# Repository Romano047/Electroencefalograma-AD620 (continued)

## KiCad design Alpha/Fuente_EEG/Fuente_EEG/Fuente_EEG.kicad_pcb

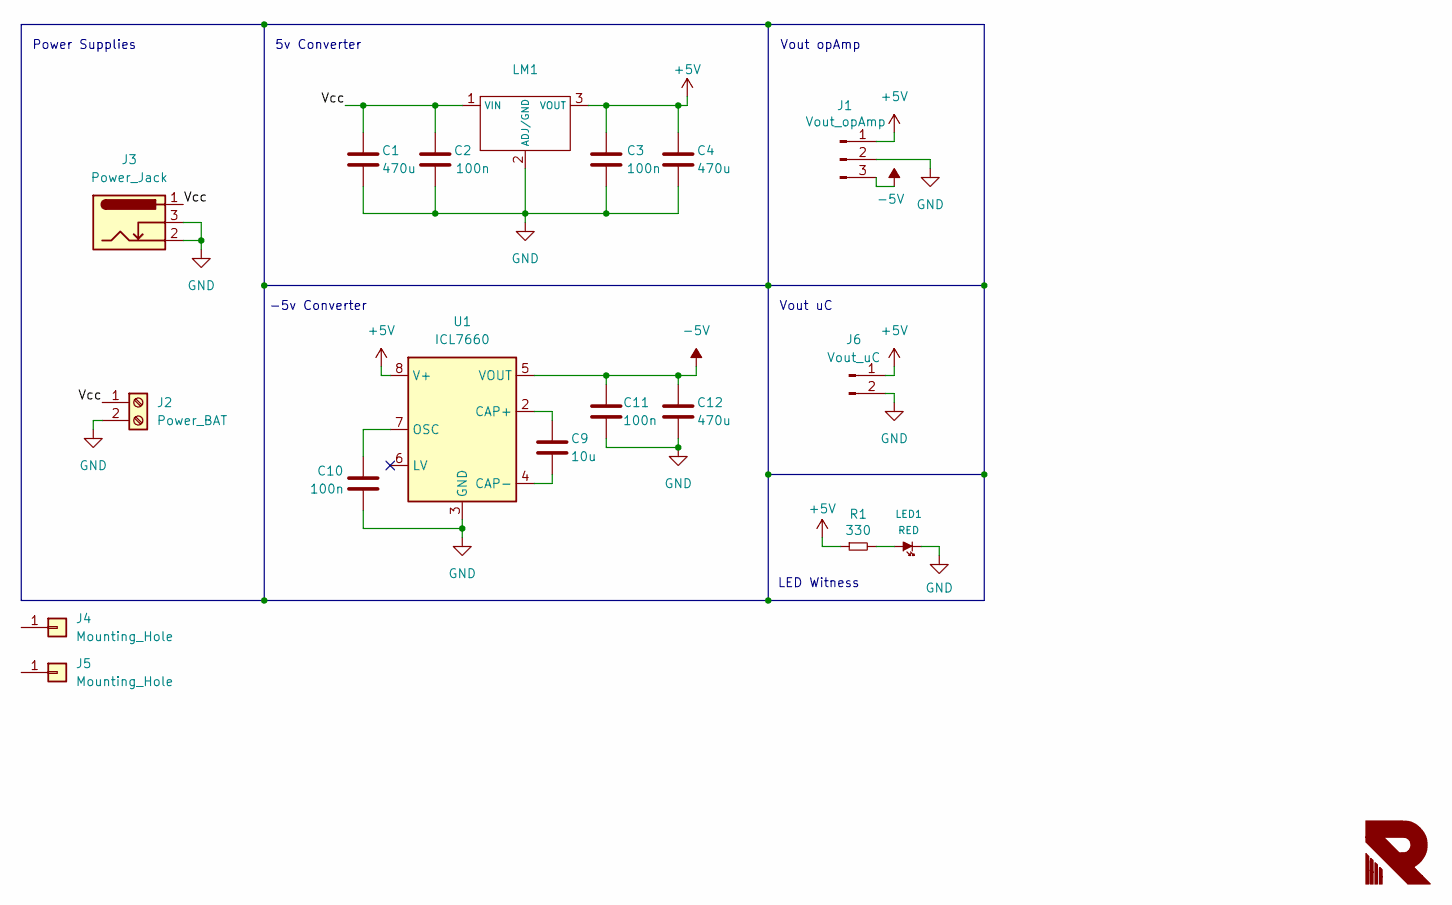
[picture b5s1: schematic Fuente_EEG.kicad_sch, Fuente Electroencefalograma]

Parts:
C1, C4, C12: 470u; CAP_ELEC_5x11mm
C2, C3, C10, C11: 100n; C_0805
C9: 10u; CAP_ELEC_5x11mm
J1: Vout_opAmp; Molex_KK-254_AE-6410-03A_1x03_P2.54mm_Vertical
J2: Power_BAT; BORNERA2_DUO
J3: Power_Jack; BarrelJack_Horizontal
J4, J5: Mounting_Hole; hole_2mm
J6: Vout_uC; Molex_KK-254_AE-6410-02A_1x02_P2.54mm_Vertical
LED1: RED; led_3mm_red
LM1: SOT223-TAB2
R1: 330; R_0805
U1: ICL7660; SOIC-8_3.9x4.9mm_P1.27mm

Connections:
+5V: C3.1, C4.1, J1.1, J6.1, LM1.3 (VOUT), R1.1, U1.8 (V+)
-5V: C11.1, C12.1, J1.3, U1.5 (VOUT)
/Vcc: C1.1, C2.1, J2.1, J3.1, LM1.1 (VIN)
GND: C1.2, C2.2, C3.2, C4.2, C10.2, C11.2, C12.2, J1.2, J2.2, J3.2, J3.3, J6.2, LED1.2 (K), LM1.2 (ADJ/GND), U1.3 (GND)
unnamed: LED1.1 (A), R1.2
unnamed: C9.1, U1.2 (CAP+)
unnamed: C9.2, U1.4 (CAP-)
unnamed: C10.1, U1.7 (OSC)

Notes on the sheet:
Power Supplies
-5v Converter
Vout opAmp
Vout uC
LED Witness
5v Converter

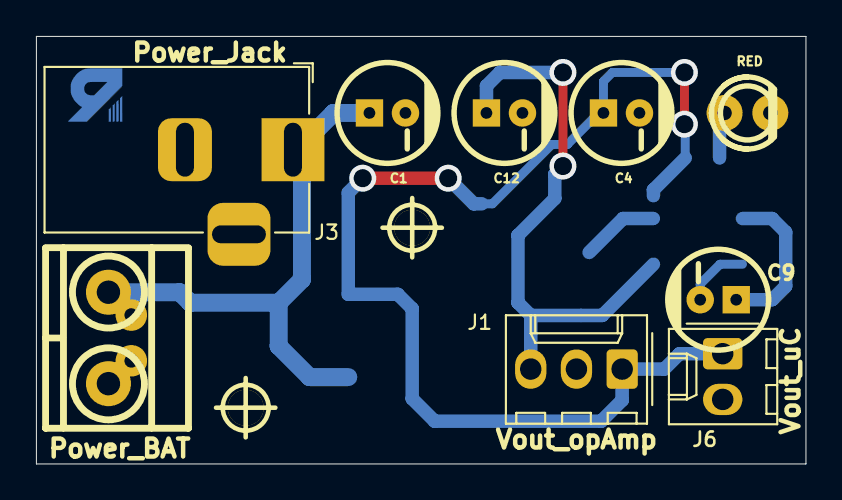
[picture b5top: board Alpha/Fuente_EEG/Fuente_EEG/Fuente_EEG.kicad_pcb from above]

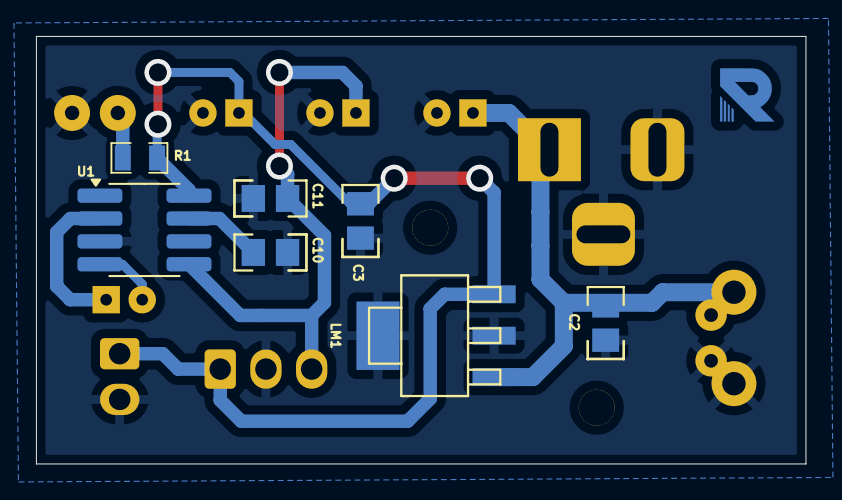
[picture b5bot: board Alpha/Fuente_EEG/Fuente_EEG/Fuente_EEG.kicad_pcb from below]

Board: 2 copper layers, 42.8 x 23.8 mm, 18 parts (7 on the bottom side), 8 nets.

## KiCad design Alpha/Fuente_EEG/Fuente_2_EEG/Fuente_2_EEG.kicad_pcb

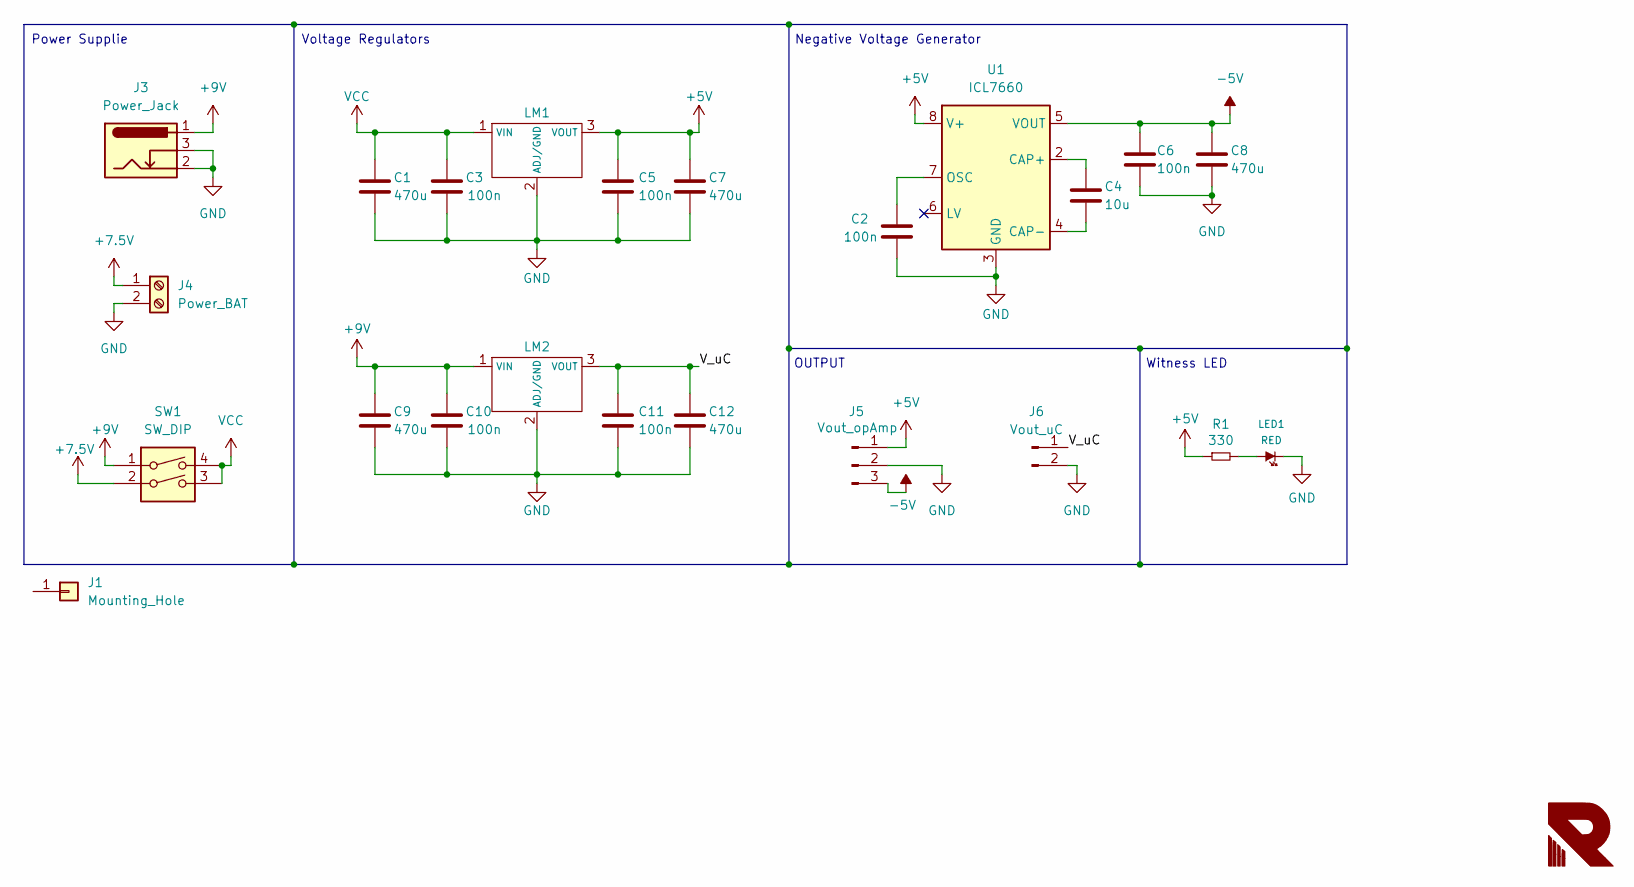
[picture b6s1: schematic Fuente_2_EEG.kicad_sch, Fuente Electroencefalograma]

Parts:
C1, C7, C8, C9, C12: 470u; CAP_ELEC_8x11.5mm
C2, C3, C5, C6, C10, C11: 100n; C_0805
C4: 10u; CAP_ELEC_5x11mm
J1: Mounting_Hole; hole_2mm
J3: Power_Jack; BarrelJack_Horizontal
J4: Power_BAT; BORNERA2_DUO
J5: Vout_opAmp; Molex_KK-254_AE-6410-03A_1x03_P2.54mm_Vertical
J6: Vout_uC; Molex_KK-254_AE-6410-02A_1x02_P2.54mm_Vertical
LED1: RED; led_3mm_red
LM1, LM2: TO-220-2
R1: 330; R_0805
SW1: SW_DIP; SW_DIP_SPSTx02_Slide_9.78x7.26mm_W7.62mm_P2.54mm
U1: ICL7660; DIP-8

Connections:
+5V: C5.1, C7.1, J5.1, LM1.3 (VOUT), R1.1, U1.8 (V+)
+7.5V: J4.1, SW1.2
+9V: C9.1, C10.1, J3.1, LM2.1 (VIN), SW1.1
-5V: C6.1, C8.1, J5.3, U1.5 (VOUT)
/V_uC: C11.1, C12.1, J6.1, LM2.3 (VOUT)
GND: C1.2, C2.2, C3.2, C5.2, C6.2, C7.2, C8.2, C9.2, C10.2, C11.2, C12.2, J3.2, J3.3, J4.2, J5.2, J6.2, LED1.2 (K), LM1.2 (ADJ/GND), LM2.2 (ADJ/GND), U1.3 (GND)
unnamed: LED1.1 (A), R1.2
unnamed: C4.1, U1.2 (CAP+)
unnamed: C4.2, U1.4 (CAP-)
unnamed: C2.1, U1.7 (OSC)
VCC: C1.1, C3.1, LM1.1 (VIN), SW1.3, SW1.4

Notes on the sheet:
Power Supplie
Witness LED
Voltage Regulators
OUTPUT
Negative Voltage Generator

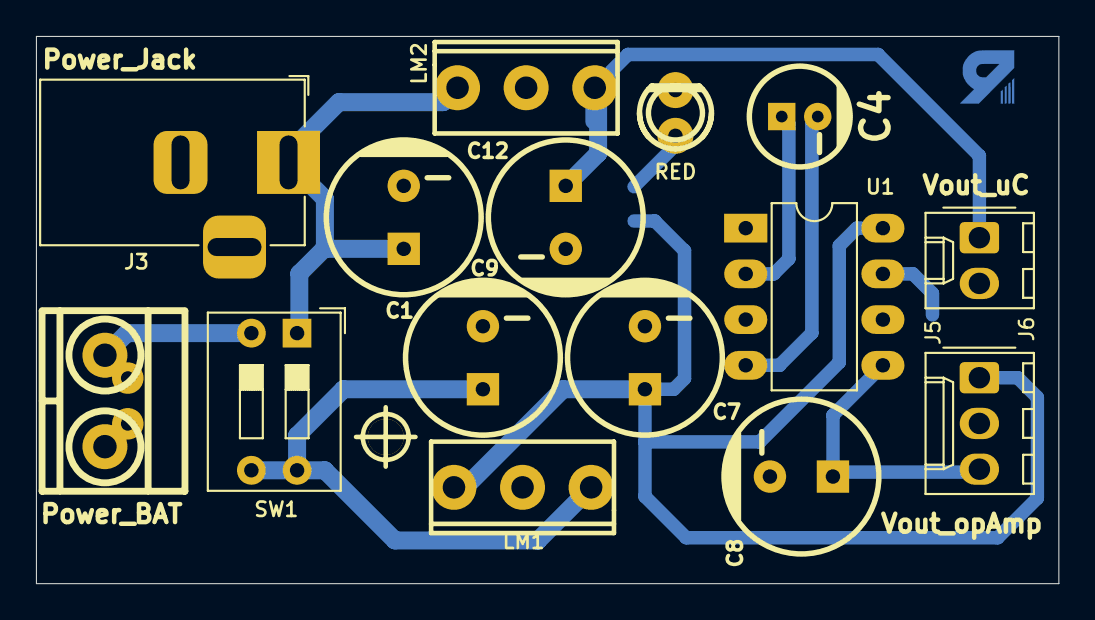
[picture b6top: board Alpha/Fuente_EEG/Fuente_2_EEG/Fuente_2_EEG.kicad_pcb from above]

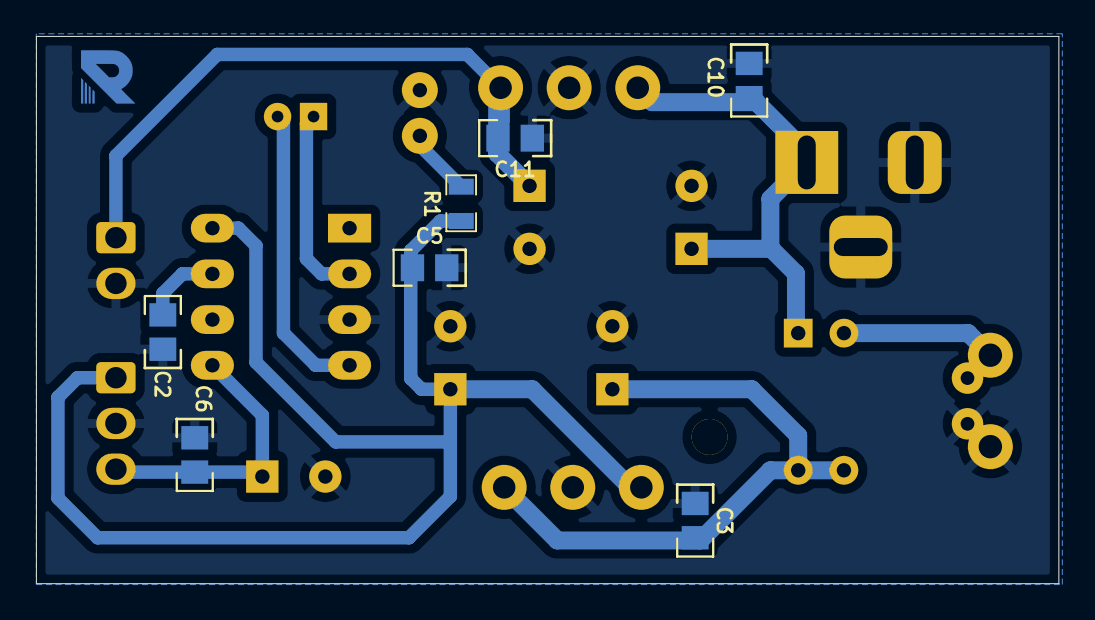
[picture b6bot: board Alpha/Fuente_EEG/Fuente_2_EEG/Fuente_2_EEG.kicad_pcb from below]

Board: 2 copper layers, 56.8 x 30.4 mm, 23 parts (7 on the bottom side), 11 nets.

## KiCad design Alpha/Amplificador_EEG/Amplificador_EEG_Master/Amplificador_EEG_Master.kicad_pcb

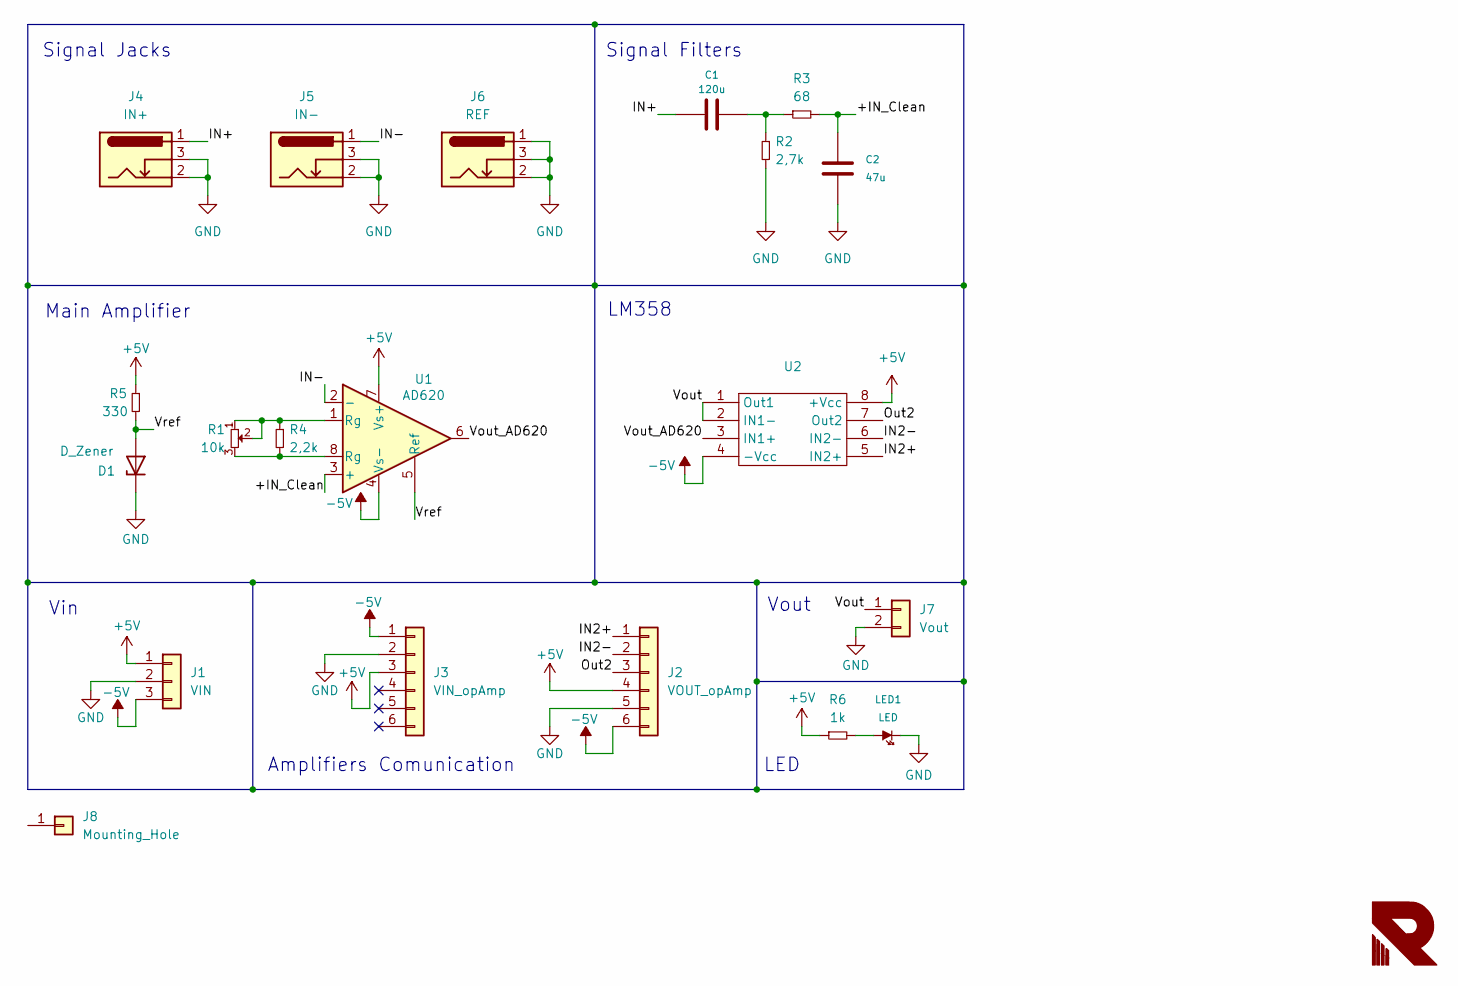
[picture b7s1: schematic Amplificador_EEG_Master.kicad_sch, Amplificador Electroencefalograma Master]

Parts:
C1: 120u; CAP_ELEC_5x11mm
C2: 47u; CAP_ELEC_5x11mm
D1: D_Zener; RES0.2
J1: VIN; Molex_KK-254_AE-6410-03A_1x03_P2.54mm_Vertical
J2: VOUT_opAmp; Molex_KK-254_AE-6410-06A_1x06_P2.54mm_Vertical
J3: VIN_opAmp; Molex_KK-254_AE-6410-06A_1x06_P2.54mm_Vertical
J4: IN+; BarrelJack_Horizontal
J5: IN-; BarrelJack_Horizontal
J6: REF; BarrelJack_Horizontal
J7: Vout; Molex_KK-254_AE-6410-02A_1x02_P2.54mm_Vertical
J8: Mounting_Hole; hole_2mm
LED1: LED; LED_1206
R1: 10k; Potenciometer_Trimpot
R2: 2,7k; RES0.3
R3: 68; RES0.3
R4: 2,2k; RES0.3
R5: 330; R_0805
R6: 1k; R_0805
U1: AD620; DIP-8_W7.62mm_LongPads
U2: SSOP-8

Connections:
+5V: J1.1, J2.4, J3.3, R5.1, R6.1, U1.7 (Vs+), U2.8 (+Vcc)
-5V: J1.3, J2.6, J3.1, U1.4 (Vs-), U2.4 (-Vcc)
/+IN_Clean: C2.2, R3.2, U1.3 (+)
/IN2+: J2.1, U2.5 (IN2+)
/IN2-: J2.2, U2.6 (IN2-)
/IN+: C1.1, J4.1
/IN-: J5.1, U1.2 (-)
/Out2: J2.3, U2.7 (Out2)
/Vout: J7.1, U2.1 (Out1), U2.2 (IN1-)
/Vout_AD620: U1.6, U2.3 (IN1+)
/Vref: D1.2 (A), R5.2, U1.5 (Ref)
GND: C2.1, D1.1 (K), J1.2, J2.5, J3.2, J4.2, J4.3, J5.2, J5.3, J6.1, J6.2, J6.3, J7.2, LED1.2 (K), R2.2
unnamed: C1.2, R2.1, R3.1
unnamed: LED1.1 (A), R6.2
unnamed: R1.1, R1.2, R4.1, U1.1 (Rg)
unnamed: R1.3, R4.2, U1.8 (Rg)

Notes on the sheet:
Vin
Signal Filters
LED
Vout
LM358
Signal Jacks
Main Amplifier
Amplifiers Comunication

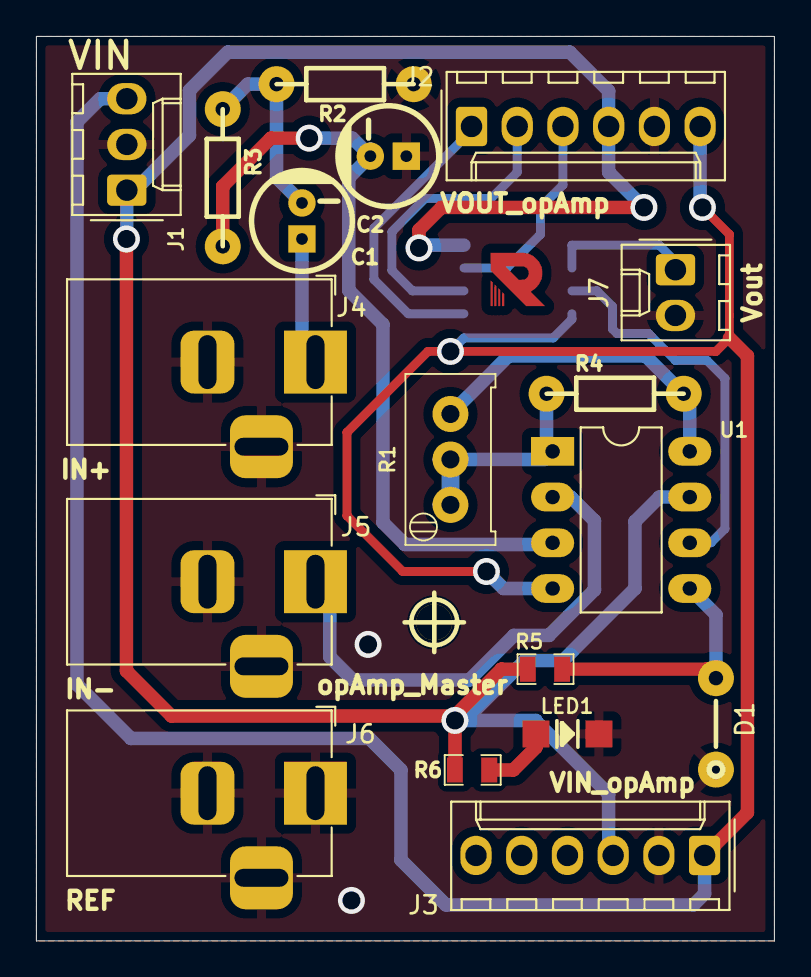
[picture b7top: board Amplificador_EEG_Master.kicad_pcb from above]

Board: 2 copper layers, 41.0 x 50.2 mm, 20 parts (1 on the bottom side), 16 nets.

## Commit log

2025-05-16 Create Software
2025-06-21 Carpeta Beta
2025-06-21 Limpieza de rama Alpha
2025-06-21 Archivos de versión Alpha
2025-06-21 Archivos versión Beta
2025-06-21 Limpieza de Rama Beta
2025-06-21 Última Actualización de Hardware
2025-06-23 Actualización Componentes PCBs
2025-06-27 Trazado de PCBs
2025-06-27 main Hardware update
2025-06-27 Update README.md
    README 2.2 Beta
2025-07-10 Actualización Amplificador
2025-07-10 Actualización de Dimensiones
2025-08-20 PCBs Update
2025-08-20 Simulador
2025-08-20 Simulación Alpha
2025-08-22 Actual
2025-09-17 Fuente Update
2025-11-30 V4.0
